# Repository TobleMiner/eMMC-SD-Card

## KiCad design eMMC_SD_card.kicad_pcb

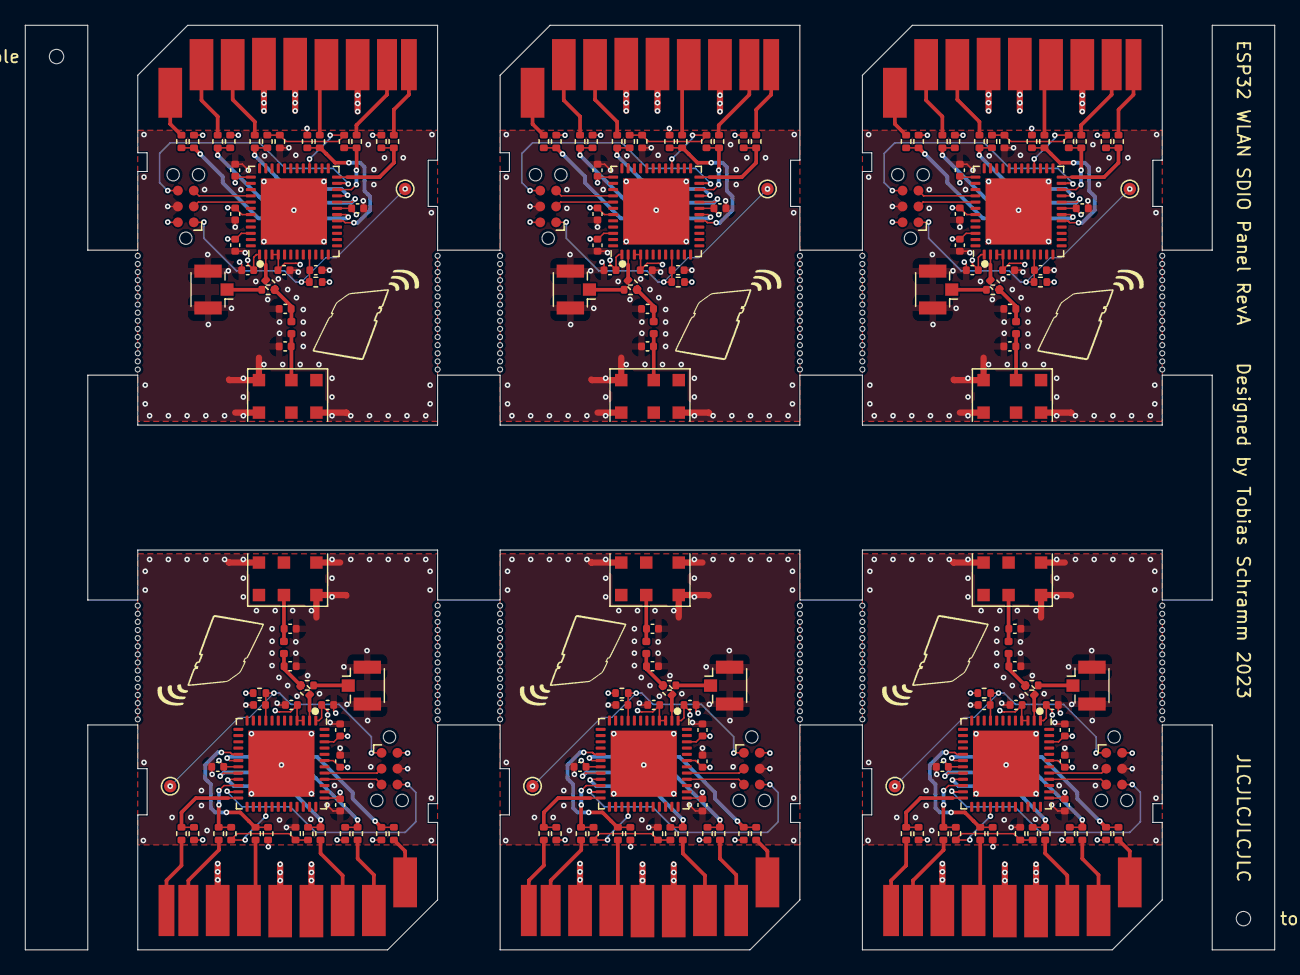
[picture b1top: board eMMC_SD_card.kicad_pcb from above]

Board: 4 copper layers, 100.0 x 74.0 mm, 374 parts (0 on the bottom side), 128 nets.

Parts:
AE1, AE2, AE3, AE4, AE5, AE6: Antenna_Chip; SR4W035
C1, C7, C10, C16, C19, C25, C28, C34, C37, C43, C46, C52: 100nF; C_0402_1005Metric
C2, C3, C4, C5, C6, C11, C12, C13, C14, C15, C20, C21, C22, C23, C24, C29, C30, C31, C32, C33, C38, C39, C40, C41, C42, C47, C48, C49, C50, C51: 2.2uF; C_0402_1005Metric
C8, C9, C17, C18, C26, C27, C35, C36, C44, C45, C53, C54: DNP; C_0402_1005Metric
H1, H2, H3, H4, H5, H6, H7, H8, H9, H10, H11, H12, H13, H14, H15, H16, H17, H18, H19, H20, H21, H22, H23, H24, H25, H26, H27, H28, H29, H30, H31, H32, H33, H34, H35, H36, H37, H38, H39, H40, H41, H42, H43, H44, H45, H46, H47, H48, H49, H50, H51, H52, H53, H54, H55, H56, H57, H58, H59, H60, H61, H62, H63, H64, H65, H66, H67, H68, H69, H70, H71, H72, H73, H74, H75, H76, H77, H78, H79, H80, H81, H82, H83, H84, H85, H86, H87, H88, H89, H90, H91, H92, H93, H94, H95, H96, H97, H98, H99, H100, H101, H102, H103, H104, H105, H106, H107, H108, H109, H110, H111, H112, H113, H114, H115, H116, H117, H118, H119, H120, H121, H122, H123, H124, H125, H126, H127, H128, H129, H130, H131, H132, H133, H134, H135, H136, H137, H138, H139, H140, H141, H142, H143, H144, H145, H146, H147, H148, H149, H150, H151, H152, H153, H154, H155, H156, H157, H158, H159, H160, H161, H162, H163, H164, H165, H166, H167, H168, H169, H170, H171, H172, H173, H174, H175, H176, H177, H178, H179, H180: MountingHole; Perforation_0.4mm
H181, H182: MountingHole; ToolingHole_JLCSMT
J1, J3, J5, J7, J9, J11: SD_Card; SD
J2, J4, J6, J8, J10, J12: Conn_Coaxial; U.FL_Hirose_U.FL-R-SMT-1_Vertical
L1, L2, L3, L4, L5, L6: 0R; L_0402_1005Metric
R1, R2, R3, R4, R5, R7, R17, R18, R19, R20, R21, R22, R33, R34, R35, R36, R37, R38, R49, R50, R51, R52, R53, R54, R65, R66, R67, R68, R69, R70, R81, R82, R83, R84, R85, R86: 33R; R_0402_1005Metric
R6, R8, R9, R10, R11, R12, R13, R14, R23, R24, R25, R26, R27, R30, R31, R32, R39, R40, R41, R42, R43, R46, R47, R48, R55, R56, R57, R58, R59, R62, R63, R64, R71, R72, R73, R74, R75, R78, R79, R80, R87, R88, R89, R90, R91, R94, R95, R96: 10k; R_0402_1005Metric
R15, R16, R28, R29, R44, R45, R60, R61, R76, R77, R92, R93: 0R; R_0402_1005Metric
TP1, TP2, TP3, TP4, TP5, TP6: RESET; TestPoint_Pad_D1.0mm
U1, U4, U6, U8, U10, U12: ESP32-PICO-D4; QFN-48-1EP_7x7mm_P0.5mm_EP5.3x5.3mm
U2, U3, U5, U7, U9, U11: TagConnect_TC2030_ESP32; Tag-Connect_TC2030-IDC-NL_2x03_P1.27mm_Vertical

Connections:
+3V3: C2.1, C3.1, C4.1, C5.1, C6.1, C7.1, C11.1, C12.1, C13.1, C14.1, C15.1, C16.1, C20.1, C21.1, C22.1, C23.1, C24.1, C25.1, C29.1, C30.1, C31.1, C32.1, C33.1, C34.1, C38.1, C39.1, C40.1, C41.1, C42.1, C43.1, C47.1, C48.1, C49.1, C50.1, C51.1, C52.1, J1.4 (VDD), J3.4 (VDD), J5.4 (VDD), J7.4 (VDD), J9.4 (VDD), J11.4 (VDD), R6.1, R8.1, R9.1, R10.1, R11.1, R23.1, R24.1, R25.1, R26.1, R27.1, R39.1, R40.1, R41.1, R42.1, R43.1, R55.1, R56.1, R57.1, R58.1, R59.1, R71.1, R72.1, R73.1, R74.1, R75.1, R87.1, R88.1, R89.1, R90.1, R91.1, U1.1 (VDDA), U1.3 (VDDA3P3), U1.4 (VDDA3P3), U1.19 (VDD3P3_RTC), U1.37 (VDD3P3_CPU), U1.43 (VDDA), U1.46 (VDDA), U2.2 (VDD), U3.2 (VDD), U4.1 (VDDA), U4.3 (VDDA3P3), U4.4 (VDDA3P3), U4.19 (VDD3P3_RTC), U4.37 (VDD3P3_CPU), U4.43 (VDDA), U4.46 (VDDA), U5.2 (VDD), U6.1 (VDDA), U6.3 (VDDA3P3), U6.4 (VDDA3P3), U6.19 (VDD3P3_RTC), U6.37 (VDD3P3_CPU), U6.43 (VDDA), U6.46 (VDDA), U7.2 (VDD), U8.1 (VDDA), U8.3 (VDDA3P3), U8.4 (VDDA3P3), U8.19 (VDD3P3_RTC), U8.37 (VDD3P3_CPU), U8.43 (VDDA), U8.46 (VDDA), U9.2 (VDD), U10.1 (VDDA), U10.3 (VDDA3P3), U10.4 (VDDA3P3), U10.19 (VDD3P3_RTC), U10.37 (VDD3P3_CPU), U10.43 (VDDA), U10.46 (VDDA), U11.2 (VDD), U12.1 (VDDA), U12.3 (VDDA3P3), U12.4 (VDDA3P3), U12.19 (VDD3P3_RTC), U12.37 (VDD3P3_CPU), U12.43 (VDDA), U12.46 (VDDA)
/Adapter 1/CLK: R1.1, R9.2, U1.17 (IO14)
/Adapter 1/CMD: R4.1, R13.2, U1.21 (IO15)
/Adapter 1/DAT0: R3.1, R12.1, U1.22 (IO2)
/Adapter 1/DAT1: R5.1, R10.2, U1.24 (IO4)
/Adapter 1/DAT2: R6.2, R7.1, U1.18 (IO12)
/Adapter 1/DAT3: R2.1, R8.2, U1.20 (IO13)
/Adapter 1/EN: C1.1, R11.2, TP1.1, U1.9 (EN), U2.1 (ESP_EN)
/Adapter 1/IO0: U1.23 (IO0), U2.6 (ESP_IO0)
/Adapter 1/RXD: U1.40 (U0RXD/IO3), U2.5 (ESP_RXD)
/Adapter 1/TXD: U1.41 (U0TXD/IO1), U2.3 (ESP_TXD)
/Adapter 2/CLK: R18.1, R25.2, U4.17 (IO14)
/Adapter 2/CMD: R21.1, R31.2, U4.21 (IO15)
/Adapter 2/DAT0: R20.1, R30.1, U4.22 (IO2)
/Adapter 2/DAT1: R22.1, R26.2, U4.24 (IO4)
/Adapter 2/DAT2: R17.1, R23.2, U4.18 (IO12)
/Adapter 2/DAT3: R19.1, R24.2, U4.20 (IO13)
/Adapter 2/EN: C10.1, R27.2, TP2.1, U3.1 (ESP_EN), U4.9 (EN)
/Adapter 2/IO0: U3.6 (ESP_IO0), U4.23 (IO0)
/Adapter 2/RXD: U3.5 (ESP_RXD), U4.40 (U0RXD/IO3)
/Adapter 2/TXD: U3.3 (ESP_TXD), U4.41 (U0TXD/IO1)
/Adapter 3/CLK: R34.1, R41.2, U6.17 (IO14)
/Adapter 3/CMD: R37.1, R47.2, U6.21 (IO15)
/Adapter 3/DAT0: R36.1, R46.1, U6.22 (IO2)
/Adapter 3/DAT1: R38.1, R42.2, U6.24 (IO4)
/Adapter 3/DAT2: R33.1, R39.2, U6.18 (IO12)
/Adapter 3/DAT3: R35.1, R40.2, U6.20 (IO13)
/Adapter 3/EN: C19.1, R43.2, TP3.1, U5.1 (ESP_EN), U6.9 (EN)
/Adapter 3/IO0: U5.6 (ESP_IO0), U6.23 (IO0)
/Adapter 3/RXD: U5.5 (ESP_RXD), U6.40 (U0RXD/IO3)
/Adapter 3/TXD: U5.3 (ESP_TXD), U6.41 (U0TXD/IO1)
/Adapter 4/CLK: R50.1, R57.2, U8.17 (IO14)
/Adapter 4/CMD: R53.1, R63.2, U8.21 (IO15)
/Adapter 4/DAT0: R52.1, R62.1, U8.22 (IO2)
/Adapter 4/DAT1: R54.1, R58.2, U8.24 (IO4)
/Adapter 4/DAT2: R49.1, R55.2, U8.18 (IO12)
/Adapter 4/DAT3: R51.1, R56.2, U8.20 (IO13)
/Adapter 4/EN: C28.1, R59.2, TP4.1, U7.1 (ESP_EN), U8.9 (EN)
/Adapter 4/IO0: U7.6 (ESP_IO0), U8.23 (IO0)
/Adapter 4/RXD: U7.5 (ESP_RXD), U8.40 (U0RXD/IO3)
/Adapter 4/TXD: U7.3 (ESP_TXD), U8.41 (U0TXD/IO1)
/Adapter 5/CLK: R66.1, R73.2, U10.17 (IO14)
/Adapter 5/CMD: R69.1, R79.2, U10.21 (IO15)
/Adapter 5/DAT0: R68.1, R78.1, U10.22 (IO2)
/Adapter 5/DAT1: R70.1, R74.2, U10.24 (IO4)
/Adapter 5/DAT2: R65.1, R71.2, U10.18 (IO12)
/Adapter 5/DAT3: R67.1, R72.2, U10.20 (IO13)
/Adapter 5/EN: C37.1, R75.2, TP5.1, U9.1 (ESP_EN), U10.9 (EN)
/Adapter 5/IO0: U9.6 (ESP_IO0), U10.23 (IO0)
/Adapter 5/RXD: U9.5 (ESP_RXD), U10.40 (U0RXD/IO3)
/Adapter 5/TXD: U9.3 (ESP_TXD), U10.41 (U0TXD/IO1)
/Adapter 6/CLK: R82.1, R89.2, U12.17 (IO14)
/Adapter 6/CMD: R85.1, R95.2, U12.21 (IO15)
/Adapter 6/DAT0: R84.1, R94.1, U12.22 (IO2)
/Adapter 6/DAT1: R86.1, R90.2, U12.24 (IO4)
/Adapter 6/DAT2: R81.1, R87.2, U12.18 (IO12)
/Adapter 6/DAT3: R83.1, R88.2, U12.20 (IO13)
/Adapter 6/EN: C46.1, R91.2, TP6.1, U11.1 (ESP_EN), U12.9 (EN)
/Adapter 6/IO0: U11.6 (ESP_IO0), U12.23 (IO0)
/Adapter 6/RXD: U11.5 (ESP_RXD), U12.40 (U0RXD/IO3)
/Adapter 6/TXD: U11.3 (ESP_TXD), U12.41 (U0TXD/IO1)
GND: AE1.2 (PCB_Trace), AE2.2 (PCB_Trace), AE3.2 (PCB_Trace), AE4.2 (PCB_Trace), AE5.2 (PCB_Trace), AE6.2 (PCB_Trace), C1.2, C2.2, C3.2, C4.2, C5.2, C6.2, C7.2, C8.2, C9.2, C10.2, C11.2, C12.2, C13.2, C14.2, C15.2, C16.2, C17.2, C18.2, C19.2, C20.2, C21.2, C22.2, C23.2, C24.2, C25.2, C26.2, C27.2, C28.2, C29.2, C30.2, C31.2, C32.2, C33.2, C34.2, C35.2, C36.2, C37.2, C38.2, C39.2, C40.2, C41.2, C42.2, C43.2, C44.2, C45.2, C46.2, C47.2, C48.2, C49.2, C50.2, C51.2, C52.2, C53.2, C54.2, J1.3 (VSS), J1.6 (VSS), J2.2 (Ext), J3.3 (VSS), J3.6 (VSS), J4.2 (Ext), J5.3 (VSS), J5.6 (VSS), J6.2 (Ext), J7.3 (VSS), J7.6 (VSS), J8.2 (Ext), J9.3 (VSS), J9.6 (VSS), J10.2 (Ext), J11.3 (VSS), J11.6 (VSS), J12.2 (Ext), R14.2, R32.2, R48.2, R64.2, R80.2, R96.2, U1.49 (GND), U2.4 (GND), U3.4 (GND), U4.49 (GND), U5.4 (GND), U6.49 (GND), U7.4 (GND), U8.49 (GND), U9.4 (GND), U10.49 (GND), U11.4 (GND), U12.49 (GND)
unnamed: AE1.1 (FEED), C9.1, L1.2
unnamed: AE2.1 (FEED), C18.1, L2.2
unnamed: AE3.1 (FEED), C27.1, L3.2
unnamed: AE4.1 (FEED), C36.1, L4.2
unnamed: AE5.1 (FEED), C45.1, L5.2
unnamed: AE6.1 (FEED), C54.1, L6.2
unnamed: C8.1, L1.1, R15.2, R16.1
unnamed: C17.1, L2.1, R28.2, R29.1
unnamed: C26.1, L3.1, R44.2, R45.1
unnamed: C35.1, L4.1, R60.2, R61.1
unnamed: C44.1, L5.1, R76.2, R77.1
unnamed: C53.1, L6.1, R92.2, R93.1
unnamed: J1.1 (CD/DAT3), R2.2
unnamed: J1.2 (CMD), R4.2
unnamed: J1.5 (CLK), R1.2
unnamed: J1.7 (DAT0), R3.2
unnamed: J1.8 (DAT1), R5.2
unnamed: J1.9 (DAT2), R7.2
unnamed: J2.1 (In), R16.2
unnamed: J3.1 (CD/DAT3), R19.2
unnamed: J3.2 (CMD), R21.2
unnamed: J3.5 (CLK), R18.2
unnamed: J3.7 (DAT0), R20.2
unnamed: J3.8 (DAT1), R22.2
unnamed: J3.9 (DAT2), R17.2
unnamed: J4.1 (In), R29.2
unnamed: J5.1 (CD/DAT3), R35.2
unnamed: J5.2 (CMD), R37.2
unnamed: J5.5 (CLK), R34.2
unnamed: J5.7 (DAT0), R36.2
unnamed: J5.8 (DAT1), R38.2
unnamed: J5.9 (DAT2), R33.2
unnamed: J6.1 (In), R45.2
unnamed: J7.1 (CD/DAT3), R51.2
unnamed: J7.2 (CMD), R53.2
unnamed: J7.5 (CLK), R50.2
unnamed: J7.7 (DAT0), R52.2
unnamed: J7.8 (DAT1), R54.2
unnamed: J7.9 (DAT2), R49.2
unnamed: J8.1 (In), R61.2
unnamed: J9.1 (CD/DAT3), R67.2
unnamed: J9.2 (CMD), R69.2
unnamed: J9.5 (CLK), R66.2
unnamed: J9.7 (DAT0), R68.2
unnamed: J9.8 (DAT1), R70.2
unnamed: J9.9 (DAT2), R65.2
unnamed: J10.1 (In), R77.2
unnamed: J11.1 (CD/DAT3), R83.2
unnamed: J11.2 (CMD), R85.2
unnamed: J11.5 (CLK), R82.2
unnamed: J11.7 (DAT0), R84.2
unnamed: J11.8 (DAT1), R86.2
unnamed: J11.9 (DAT2), R81.2
unnamed: J12.1 (In), R93.2
unnamed: R12.2, R13.1, R14.1, U1.28 (SD2/IO9)
unnamed: R15.1, U1.2 (LNA_IN)
unnamed: R28.1, U4.2 (LNA_IN)
unnamed: R30.2, R31.1, R32.1, U4.28 (SD2/IO9)
unnamed: R44.1, U6.2 (LNA_IN)
unnamed: R46.2, R47.1, R48.1, U6.28 (SD2/IO9)
unnamed: R60.1, U8.2 (LNA_IN)
unnamed: R62.2, R63.1, R64.1, U8.28 (SD2/IO9)
unnamed: R76.1, U10.2 (LNA_IN)
unnamed: R78.2, R79.1, R80.1, U10.28 (SD2/IO9)
unnamed: R92.1, U12.2 (LNA_IN)
unnamed: R94.2, R95.1, R96.1, U12.28 (SD2/IO9)

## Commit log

2020-12-04 Introduce separate VCC and VCCq domains
2020-12-04 Panelize
2020-12-04 Add tooling holes
2020-12-04 Set SD lock to unprotected
2023-02-18 Repurpose for ESP32 WiFi SDIO card
2023-02-18 Add project icon to PCB
2023-02-18 Add edge cuts for remaining SDIO cards in panel
2023-02-18 Fix visual properties for 3D view
